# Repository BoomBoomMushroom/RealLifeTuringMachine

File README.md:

# Real Life Turing Machine
This is a real, physical, and working Turing Machine using an ESP32, off the shelf i2c components, and NFC tags. The Turing machine seems like the lowest level and most basic form of hardware imaginable, so I wanted to try my hand at making one in real life!

# Images

# Hackatime project name(s)
- RealLifeTuringMachine (8h 31m) TODO: Update this time before submitting
- PCB (2h 23m)
- ESP32_OnlineDevBoard (19m)
- SD_Card_Amazon (10m)
- VHS_Container (4m)
- Blender-VHS_Container (2m)
- Blender-TuringMachineCAD_Models (2m)

# BOM (Check BOM.md for a more in depth bill of materials)
- NFC Stickers
- NFC Reader & Writer Module
- 2x 28BYJ-48 Stepper Motors & Driver boards
- 50ft to 100ft Mylar/Polyester 16mm Film Leader
- ESP32
- SD Card Breakout Board + SD Card (optional)
- Latching Switch 6 Pin
- 3D Printer filament if 3d printing the case
- 3mm LED
- PCB to house all the electronics

TODO: Fill out the checklist and submit

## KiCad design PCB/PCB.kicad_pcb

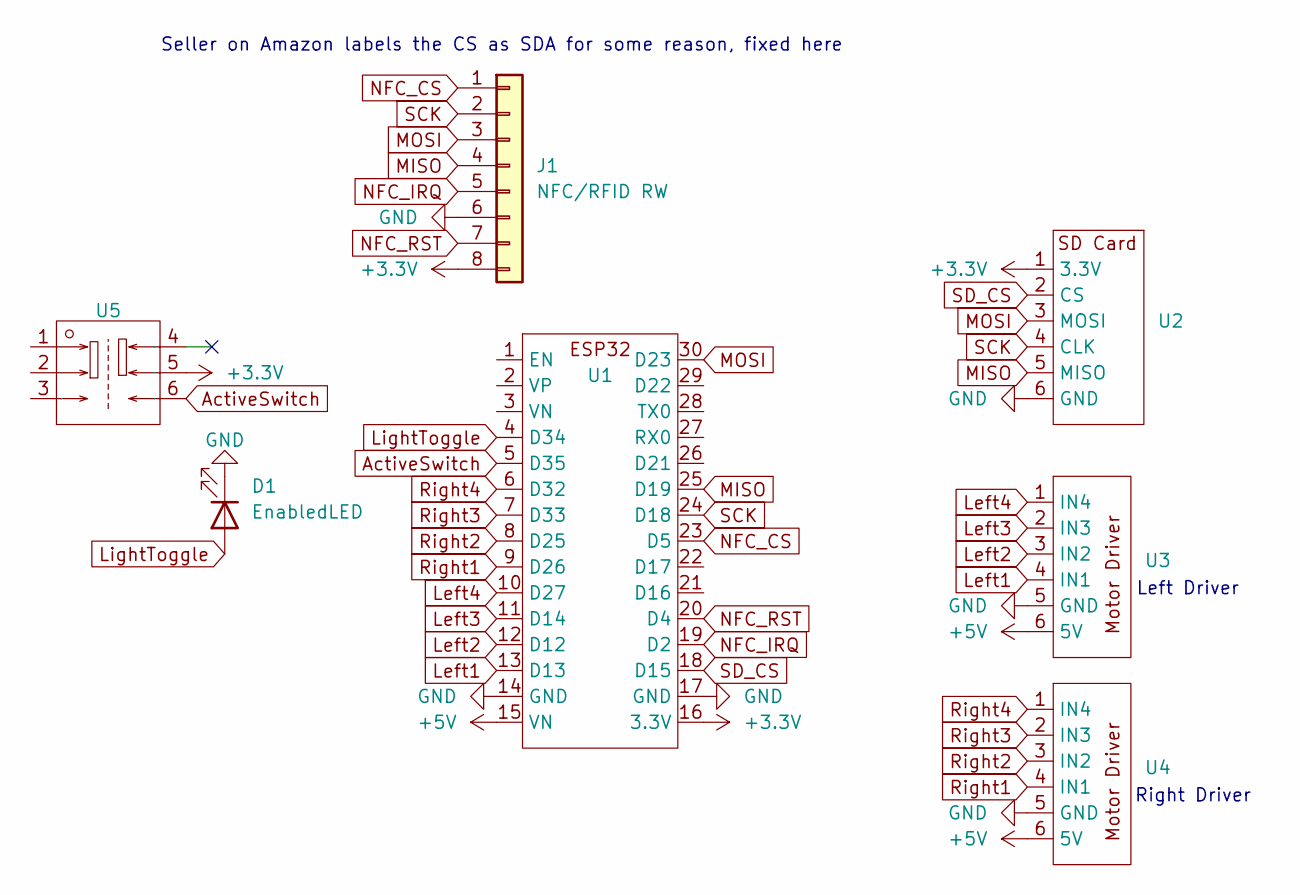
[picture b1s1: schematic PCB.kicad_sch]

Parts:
D1: EnabledLED; LED_D5.0mm
J1: NFC/RFID RW; PinHeader_1x08_P2.54mm_Vertical
U1: ESP32_OnlineDevBoard
U2, U3, U4: PinHeader_1x06_P2.54mm_Vertical
U5: SW-TH_6P-L7.0-W7.0-P2.00_KFC7070-Z; Manufacturer Part KFC7070-Z; LCSC Part Name KFC7070-Z

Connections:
+3.3V: J1.8, U1.16 (3.3V), U2.1 (3.3V), U5.5
+5V: U1.15 (VN), U3.6 (5V), U4.6 (5V)
ActiveSwitch: U1.5 (D35), U5.6
GND: D1.1 (K), J1.6, U1.14 (GND), U1.17 (GND), U2.6 (GND), U3.5 (GND), U4.5 (GND)
Left1: U1.13 (D13), U3.4 (IN1)
Left2: U1.12 (D12), U3.3 (IN2)
Left3: U1.11 (D14), U3.2 (IN3)
Left4: U1.10 (D27), U3.1 (IN4)
LightToggle: D1.2 (A), U1.4 (D34)
MISO: J1.4, U1.25 (D19), U2.5 (MISO)
MOSI: J1.3, U1.30 (D23), U2.3 (MOSI)
NFC_CS: J1.1, U1.23 (D5)
NFC_IRQ: J1.5, U1.19 (D2)
NFC_RST: J1.7, U1.20 (D4)
Right1: U1.9 (D26), U4.4 (IN1)
Right2: U1.8 (D25), U4.3 (IN2)
Right3: U1.7 (D33), U4.2 (IN3)
Right4: U1.6 (D32), U4.1 (IN4)
SCK: J1.2, U1.24 (D18), U2.4 (CLK)
SD_CS: U1.18 (D15), U2.2 (CS)

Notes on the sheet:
Seller on Amazon labels the CS as SDA for some reason, fixed here
Right Driver
Left Driver

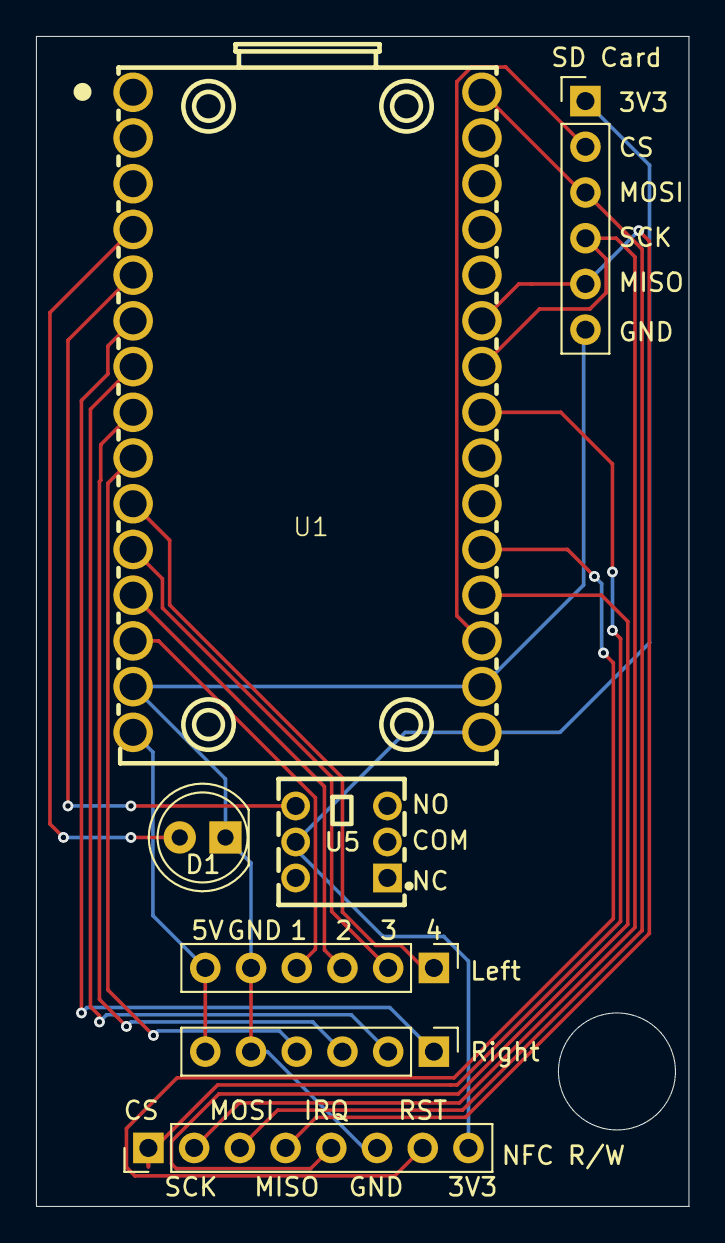
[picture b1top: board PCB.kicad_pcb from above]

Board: 2 copper layers, 36.2 x 65.0 mm, 7 parts (0 on the bottom side), 20 nets.

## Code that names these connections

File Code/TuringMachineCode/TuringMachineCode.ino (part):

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// Pins
#define LightPin 34
#define ActiveSwitchPin 35
#define NFC_IRQ_Pin 2
#define NFC_RST_Pin 4
// Motors
#define RightMotorPin4 32
#define RightMotorPin3 33
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#define MOSI 23
#define MISO 19
#define SCK 18
#define NFC_CS 5
#define SD_CS 15
SPIClass spiBus(VSPI);

// SD Card
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
// NFC
#include <MFRC522.h>
MFRC522 mfrc522(NFC_CS, NFC_RST_Pin); // Create MFRC522 instance.
MFRC522::MIFARE_Key key;

// Turing Machine
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void pinInit()
{
  pinMode(LightPin, OUTPUT);
  pinMode(NFC_RST_Pin, OUTPUT);
  pinMode(NFC_CS, OUTPUT);
  pinMode(SD_CS, OUTPUT);
  pinMode(RightMotorPin4, OUTPUT);
  pinMode(RightMotorPin3, OUTPUT);
  pinMode(RightMotorPin2, OUTPUT);
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  pinMode(ActiveSwitchPin, INPUT_PULLDOWN);

  // idk if the interrupt is necessary so i'll comment it out for now
  //attachInterrupt(digitalPinToInterrupt(NFC_IRQ_Pin), NFC_ISR, CHANGE); // idk when the interupt should be triggered so I put CHANGE, but LOW, RISING, and FALLING all are options.
}

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
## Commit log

2025-07-04 Finished PCB and working on CAD
2025-07-05 basically finished the program, need to add finishing touches to the model
2025-07-05 Finished and ready to submit
